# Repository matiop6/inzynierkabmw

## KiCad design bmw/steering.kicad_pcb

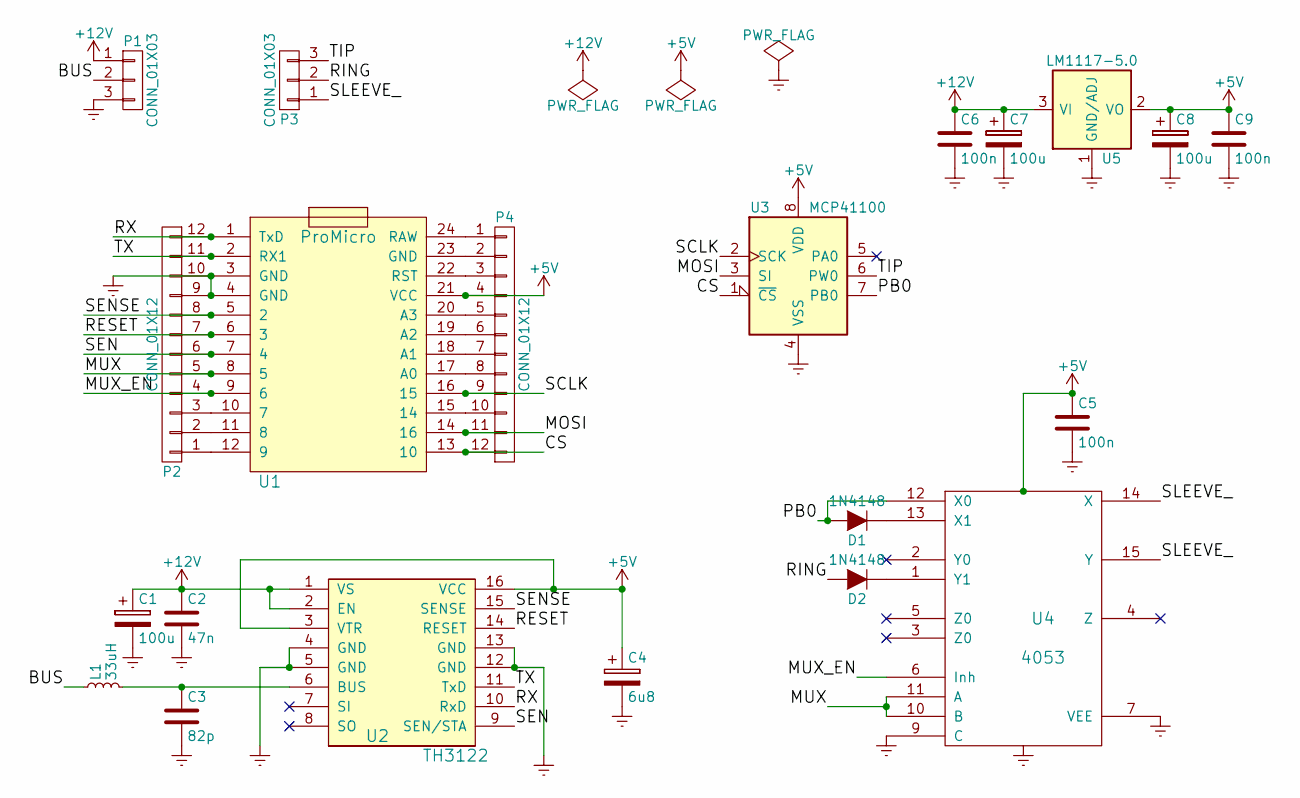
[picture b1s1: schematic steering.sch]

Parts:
C1, C7, C8: 100u; c_elec_10x10
C2: 47n; C_0603_HandSoldering
C3: 82p; C_0603_HandSoldering
C4: 6u8; c_elec_6.3x5.8
C5, C6, C9: 100n; C_0603_HandSoldering
D1, D2: 1N4148; MiniMELF_Handsoldering
L1: 33uH; C_0805_HandSoldering
P1: CONN_01X03; bornier3
P2, P4: CONN_01X12; Pin_Header_Straight_1x12
P3: CONN_01X03; Pin_Header_Straight_1x03
U1: ProMicro; Arduino_pro_micro
U2: TH3122; SO-16-L
U3: MCP41100; DIP-8_SMD
U4: 4053; SO-16-N
U5: LM1117-5.0; SOT-223

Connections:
+5V: C4.1, C5.1, C8.1, C9.1, P4.4, U1.21 (VCC), U2.3 (VTR), U2.16 (VCC), U3.8 (VDD), U4.16 (VDD), U5.2 (VO), U5.4 (VO)
+12V: C1.1, C2.1, C6.1, C7.1, P1.1, U2.1 (VS), U2.2 (EN), U5.3 (VI)
/BUS: L1.1, P1.2
/CS: P4.12, U1.13 (10), U3.1 (~CS)
/MOSI: P4.11, U1.14 (16), U3.3 (SI)
/MUX: P2.5, U1.8 (5), U4.10 (B), U4.11 (A)
/MUX_EN: P2.4, U1.9 (6), U4.6 (Inh)
/PB0: D1.2 (A), U3.7 (PB0), U4.12 (X0)
/RESET: P2.7, U1.6 (3), U2.14 (RESET)
/RING: D2.2 (A), P3.2
/RX: P2.12, U1.1 (TxD), U2.10 (RxD)
/SCLK: P4.9, U1.16 (15), U3.2 (SCK)
/SEN: P2.6, U1.7 (4), U2.9 (SEN/STA)
/SENSE: P2.8, U1.5 (2), U2.15 (SENSE)
/SLEEVE_: P3.1, U4.14 (X), U4.15 (Y)
/TIP: P3.3, U3.6 (PW0)
/TX: P2.11, U1.2 (RX1), U2.11 (TxD)
Earth: C1.2, C2.2, C3.2, C4.2, C5.2, C6.2, C7.2, C8.2, C9.2, P1.3, P2.9, P2.10, U1.3 (GND), U1.4 (GND), U2.4 (GND), U2.5 (GND), U2.12 (GND), U2.13 (GND), U3.4 (VSS), U4.7 (VEE), U4.8 (VSS), U4.9 (C), U5.1 (GND/ADJ)
unnamed: C3.1, L1.2, U2.6 (BUS)
unnamed: D1.1 (K), U4.13 (X1)
unnamed: D2.1 (K), U4.1 (Y1)
unnamed: P2.1, U1.12 (9)
unnamed: P2.2, U1.11 (8)
unnamed: P2.3, U1.10 (7)
unnamed: P4.1, U1.24 (RAW)
unnamed: P4.2, U1.23 (GND)
unnamed: P4.3, U1.22 (RST)
unnamed: P4.5, U1.20 (A3)
unnamed: P4.6, U1.19 (A2)
unnamed: P4.7, U1.18 (A1)
unnamed: P4.8, U1.17 (A0)
unnamed: P4.10, U1.15 (14)

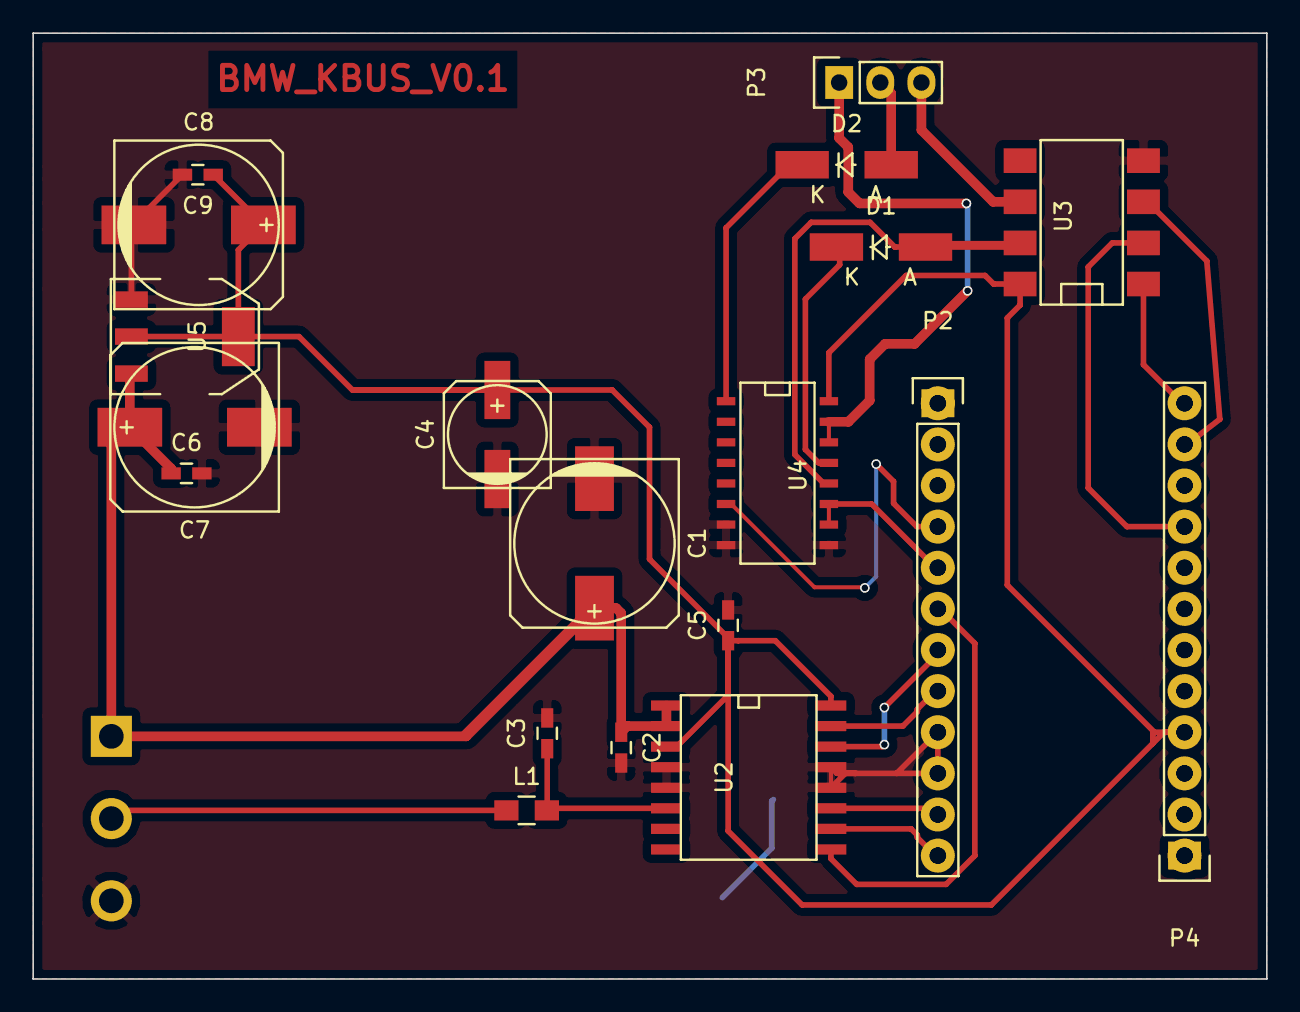
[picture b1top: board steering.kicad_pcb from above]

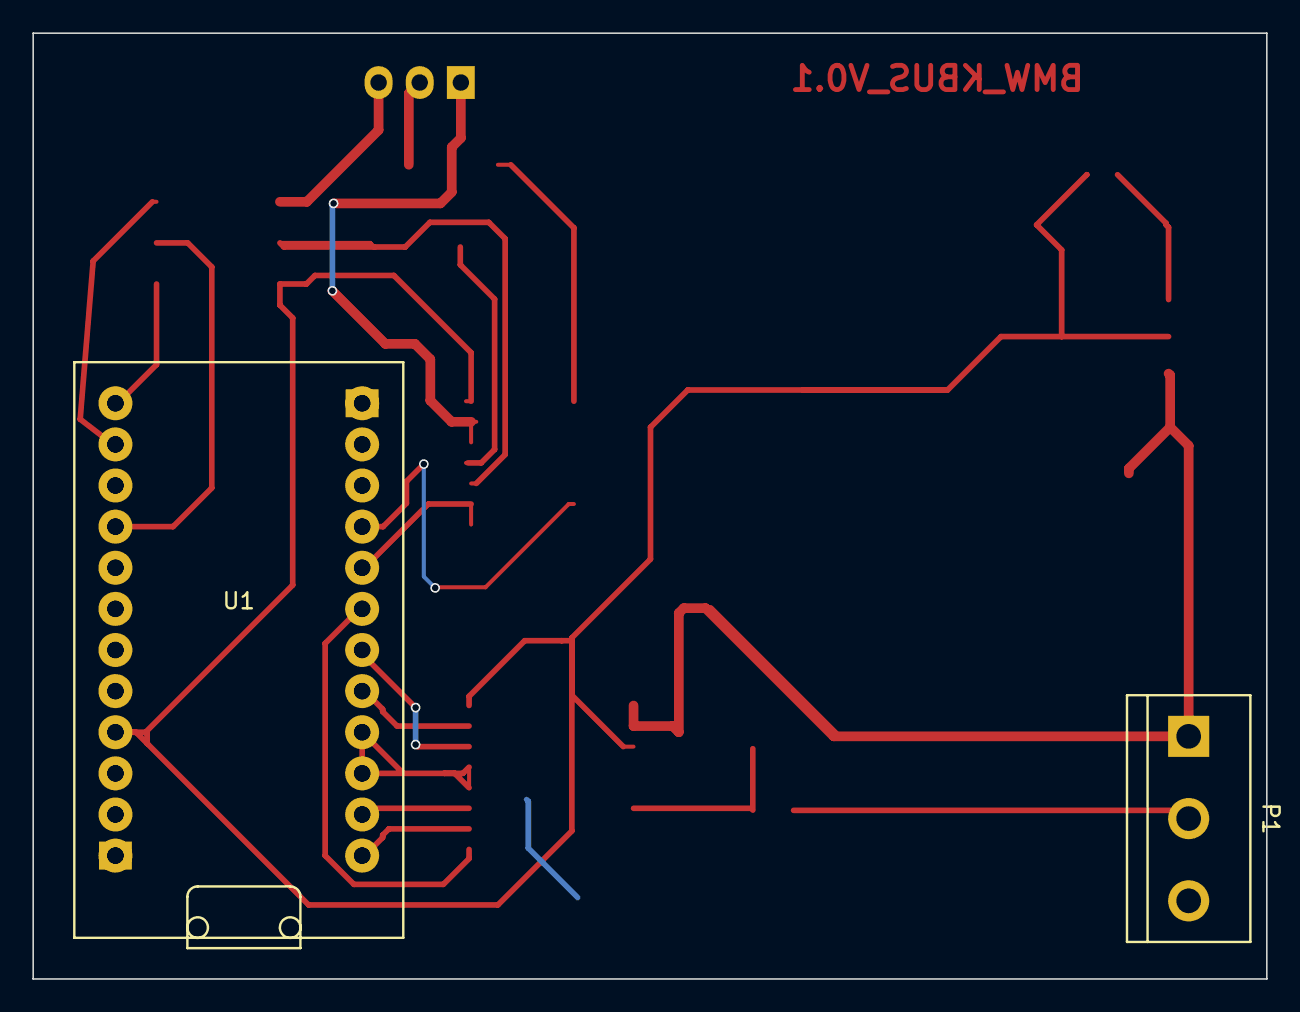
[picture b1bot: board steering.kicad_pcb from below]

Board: 2 copper layers, 76.2 x 58.4 mm, 21 parts (2 on the bottom side), 32 nets.

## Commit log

2017-03-23 Dodanie plikow projektu pcb.
2017-03-26 Wersja 0.1 plytki PCB. Nie dodano slotow na zasilanie z przetwornicy.
2017-04-19 Zrezygnowano z przetwornicy na rzecz LDO LM1117 5V. Pozostało połączyć masę układu w dwóch punktach. Poprawnie przechodzi testy DRC. Można wykonać prototyp.
